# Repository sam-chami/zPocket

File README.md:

# zPocket
> WIP

The zPocket is a modular, handheld portable Linux device with a square touchscreen as well as keyboard for input. The modularity allows you to use it as a Cyberdeck, Phone, or even satellite communicator.

## Significant features:
- Touchscreen 720x720 panel
- Blackberry Q10 Keyboard
- Raspberry Pi Compute Module 5
- Mini PCIe connector
- USB-C Dual-role Port and mini HDMI
- Magnetometer (Compass)
- Battery Charging and Gauge

## Assembly Render
Front                                                   |  Back
:------------------------------------------------------:|:--------------------------------------:
  |  

## PCB

## Documentation
The documentation is available in [this repository's wiki page](https://github.com/sam-chami/zPocket/wiki)

## License
The zPocket hardware has a "CERN Open Hardware Licence Version 2 - Strongly Reciprocal".

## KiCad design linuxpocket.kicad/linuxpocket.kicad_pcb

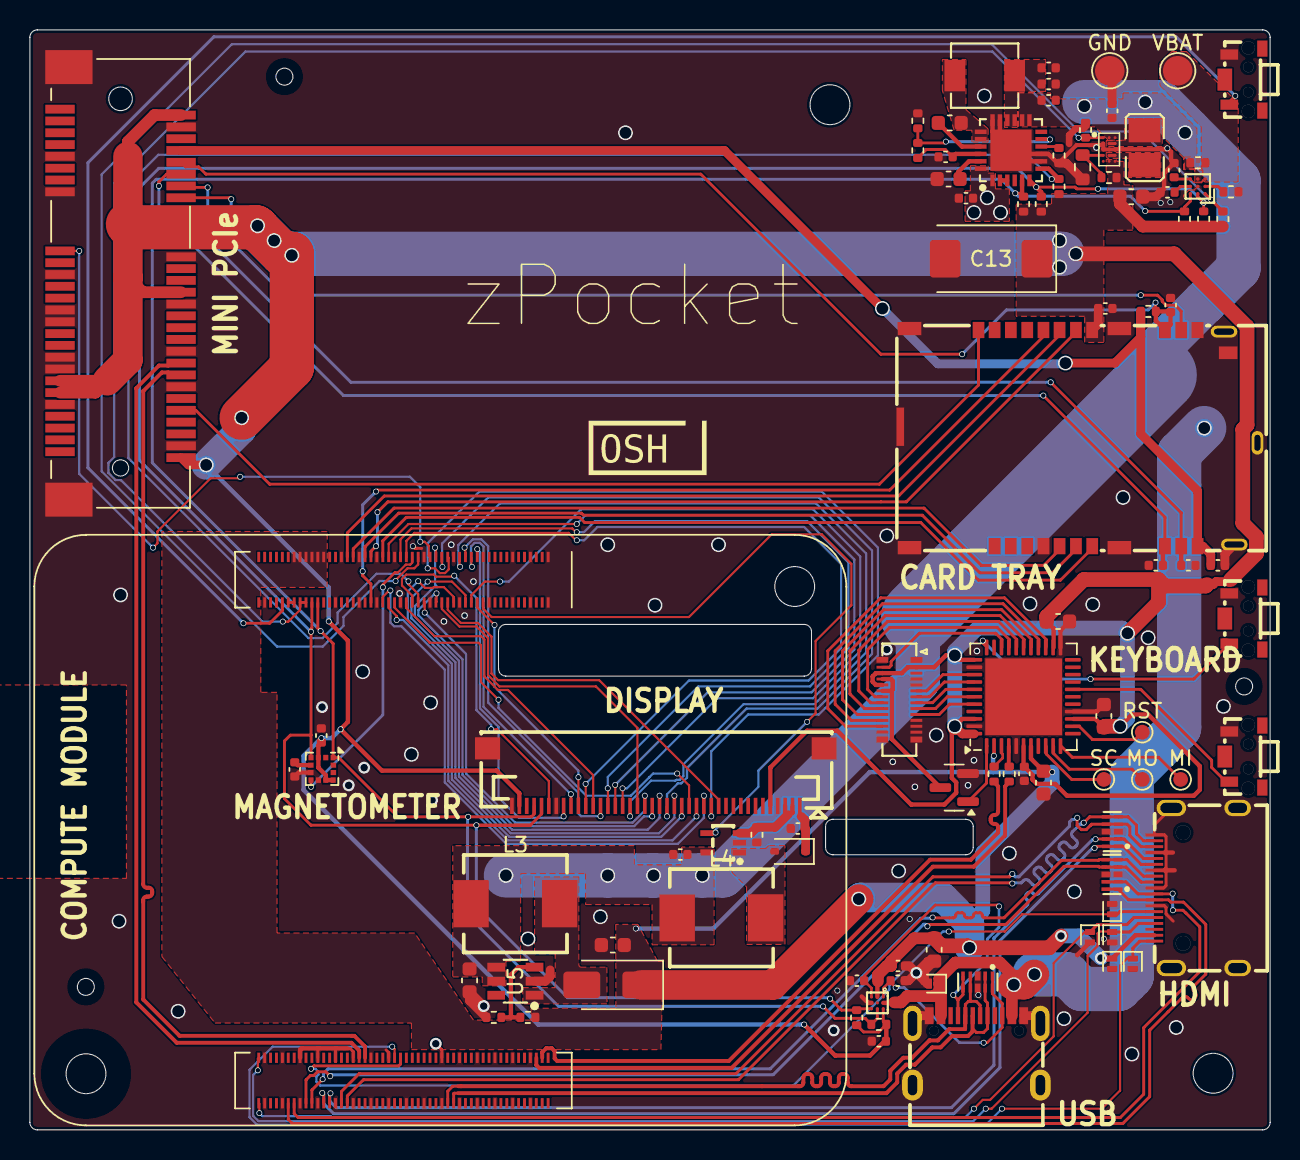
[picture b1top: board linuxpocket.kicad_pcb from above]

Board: 4 copper layers, 84.0 x 74.5 mm, 94 parts (0 on the bottom side), 112 nets.

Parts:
C1, C4, C6, C7, C11, C32: 10uF; C_0402_1005Metric
C2, C10, C17, C18, C19, C22, C27, C28: 1uF; C_0402_1005Metric
C3, C23, C24, C25: 47nF; C_0603_1608Metric
C5, C9: 4.7uF; C_0402_1005Metric
C8, C12, C20, C21, C26: 22uF; C_0603_1608Metric
C13: 470uF; CP_EIA-7343-31_Kemet-D
C14, C15, C16: 33pF; C_0402_1005Metric
C29, C30: 220pF; C_0402_1005Metric
C31: 220nF; C_0402_1005Metric
D2: D_Schottky; D_SOD-323
D3: D_Schottky; D_SMA
D4, D5, D11: TPD4E02B04DQAR; USON-10_L2.5-W1.0-P0.50-BL
D6, D7, D8, D9, D10, D12: H5VL10B; D_SOD-882
FPC1: XF2M-4015-1A_C225713; FPC-SMD_40P-P0.50_L4.9-W23.5
GND: TestPoint_Pad_D2.0mm
J1: XDSM-1035-08-KT; SIM-SMD_XDSM-1035-08_1
J2: Bus_PCI_Express_Mini; BUS_PCI_Express_Mini_Full
J3: HDMI_C_1.4; HDMI-SMD_A71-05H4-111N1
J4: USB_C_Receptacle_USB2.0_14P; USB-SMD_TYPE-C16PIN-1
L1: 2.2uH; IND-SMD_L4.4-W4.2
L2: 0.47uH; L1008
L3, L4: 4.7uH; IND-SMD_L7.0-W6.6
MI: TestPoint; TestPoint_Pad_D1.0mm
MO: TestPoint; TestPoint_Pad_D1.0mm
Module1: ComputeModule4-CM4; Raspberry-Pi-4-Compute-Module
Q1: MMBT3904; SOT-23
R1, R2, R3, R8, R9, R10, R11, R15, R16, R21: 10k; R_0402_1005Metric
R4, R22: 22; R_0402_1005Metric
R6: 120; R_0402_1005Metric
R7, R20: 15k; R_0402_1005Metric
R12: 10mΩ; R_0402_1005Metric
R13: 510k; R_0402_1005Metric
R14: 91k; R_0603_1608Metric
R18: 4.7; R_0402_1005Metric
R19: 100k; R_0402_1005Metric
R26, R27: 4.7k; R_0402_1005Metric
RST: TestPoint; TestPoint_Pad_D1.0mm
SC: TestPoint; TestPoint_Pad_D1.0mm
SW1, SW2, SW3: PUSH; SW-SMD_GT-TC020B-H035-L05
U1: BQ24295RGER; VQFN-24_L4.0-W4.0-P0.50-TL-EP2.8
U2: BQ27426YZFR; DSBGA-9_L1.5-W1.5-R3-C3-P0.50-BL
U3: TPS63805YFFR; DSBGA-15_L2.3-W1.3-R5-C3-P0.40-TL
U4: TPS61169DCKR; SC-70-5_L2.1-W1.3-P0.65-LS2.1-BR
U5: MT3608L; SOT-23-6_L2.9-W1.6-P0.95-LS2.8-BL_3
U6: FUSB302BUCX; WLCSP-9_L1.3-W1.2-R3-C3-P0.40-TL
U7: BBQ10KBD; BM14B(0.8)-24DS-0.4V(53)
U8: ATmega32U4-M; QFN-44-1EP_7x7mm_P0.5mm_EP5.2x5.2mm
U9: LIS2MDL; LGA-12_2x2mm_P0.5mm
VBAT: TestPoint_Pad_D2.0mm

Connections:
+1V8: Module1.88 (+1.8v_(Output)), Module1.90 (+1.8v_(Output))
+3V3: C1.2, C12.1, C13.1, C22.1, C23.1, C24.1, C27.2, C32.2, FPC1.5, FPC1.39, J1.16 (VDD), J2.2 (+3V3AUX), J2.24 (+3V3AUX), J2.39 (+3V3AUX), J2.41 (+3V3AUX), J2.52 (+3V3AUX), R1.1, R2.1, R3.1, R9.1, R10.1, R11.1, R13.1, R26.1, R27.1, U3.E2 (VOUT), U3.E3 (VOUT), U6.A3 (VDD), U7.2 (MIC_VDD), U7.24 (LEDA_3_4), U7.26 (LEDA_1_2), U8.6 (UCAP), U8.14 (VCC), U8.24 (AVCC), U8.34 (VCC), U8.42 (AREF), U8.44 (AVCC), U9.3 (~CS), U9.9 (Vdd), U9.10 (Vdd_IO)
+5V: C21.1, C25.1, C26.1, C28.2, D3.1 (K), D10.1 (A1), J3.18 (+5V), Module1.77 (+5v_(Input)), Module1.79 (+5v_(Input)), Module1.81 (+5v_(Input)), Module1.83 (+5v_(Input)), Module1.85 (+5v_(Input)), Module1.87 (+5v_(Input)), R19.1, U6.B1 (VCONN), U8.2 (UVCC), U8.7 (VBUS)
/Battery and Power/3V3 EN: Module1.78 (GPIO_VREF(1.8v/3.3v_Input)), Module1.84 (+3.3v_(Output)), Module1.86 (+3.3v_(Output)), R21.1, U3.A1 (EN)
/Battery and Power/BACKLIGHT: Module1.24 (GPIO26), U4.4 (CTRL)
/Battery and Power/CHARGE_INT: Module1.46 (GPIO22), R3.2, U1.7 (INT)
/Battery and Power/CHARGE_NTC: R7.1, R8.2, U1.11 (TS)
/Battery and Power/GAUGE_GPOUT: Module1.45 (GPIO24), R9.2, U2.A1 (GPOUT)
/Battery and Power/LEDA: C19.2, D2.1 (K), FPC1.1
/Battery and Power/LEDK: FPC1.2, FPC1.3, R18.1, U4.3 (FB)
/Battery and Power/REGN: C5.1, R8.1, U1.22 (REGN)
/Battery and Power/SYS: C6.1, C7.1, L1.1, U1.15 (SYS), U1.16 (SYS)
/Battery and Power/VBATT: C10.2, R12.1, U2.C1 (SRP), U2.C3 (BAT), VBAT.1
/Battery and Power/VBUS: C2.1, D12.1 (A1), J4.A4 (VBUS), J4.B9 (VBUS), U1.1 (VBUS), U1.24 (VBUS), U6.A2 (VBUS)
/Battery and Power/VBload: C4.1, C11.1, C18.2, C20.1, L3.1, L4.1, R12.2, U1.13 (BAT), U1.14 (BAT), U2.C2 (SRN), U3.A2 (VIN), U3.A3 (VIN), U4.5 (VIN), U5.4 (EN), U5.5 (VIN)
/Battery and Power/VDD: C9.1, U2.B3 (VDD)
/GPIO/DE: FPC1.13, Module1.35 (ID_SC)
/GPIO/DPI_D0: FPC1.16, Module1.54 (GPIO4)
/GPIO/DPI_D1: FPC1.17, Module1.34 (GPIO5)
/GPIO/DPI_D2: FPC1.18, Module1.30 (GPIO6)
/GPIO/DPI_D3: FPC1.19, Module1.37 (GPIO7)
/GPIO/DPI_D4: FPC1.20, Module1.39 (GPIO8)
/GPIO/DPI_D5: FPC1.21, Module1.40 (GPIO9)
/GPIO/DPI_D6: FPC1.22, Module1.44 (GPIO10)
/GPIO/DPI_D7: FPC1.23, Module1.38 (GPIO11)
/GPIO/DPI_D8: FPC1.24, Module1.31 (GPIO12)
/GPIO/DPI_D9: FPC1.25, Module1.28 (GPIO13)
/GPIO/DPI_D10: FPC1.26, Module1.55 (GPIO14)
/GPIO/DPI_D11: FPC1.27, Module1.51 (GPIO15)
/GPIO/DPI_D12: FPC1.28, Module1.29 (GPIO16)
/GPIO/DPI_D13: FPC1.29, Module1.50 (GPIO17)
/GPIO/DPI_D14: FPC1.30, Module1.49 (GPIO18)
/GPIO/DPI_D15: FPC1.31, Module1.26 (GPIO19)
/GPIO/DPI_D16: FPC1.32, Module1.27 (GPIO20)
/GPIO/DPI_D17: FPC1.33, Module1.25 (GPIO21)
/GPIO/LCD_HSYNC: FPC1.15, Module1.56 (GPIO3)
/GPIO/LCD_VSYNC: FPC1.14, Module1.58 (GPIO2)
/GPIO/MAG_INT: Module1.47 (GPIO23), U9.7 (DRDY)
/GPIO/PCLK: FPC1.12, Module1.36 (ID_SD)
/GPIO/PWR_BUT: Module1.92 (RUN_PG), SW1.1
/GPIO/RI: J2.17 (UIM_C8), Module1.41 (GPIO25)
/GPIO/SD_CLK: J1.17 (CLK), Module1.57 (SD_CLK)
/GPIO/SD_CMD: J1.15 (CMD), Module1.62 (SD_CMD)
/GPIO/SD_DAT0: J1.19 (DAT0), Module1.63 (SD_DAT0)
/GPIO/SD_DAT1: J1.20 (DAT1), Module1.67 (SD_DAT1)
/GPIO/SD_DAT2: J1.13 (DAT2), Module1.69 (SD_DAT2)
/GPIO/SD_DAT3: J1.14 (CD/DAT3), Module1.61 (SD_DAT3)
/GPIO/SIM_CLK: C14.1, J1.3 (SIM1_CLK), J2.12 (UIM_CLK)
/GPIO/SIM_IO: C15.1, J1.6 (SIM1_I/O), J2.10 (UIM_DATA), R15.2
/GPIO/SIM_RST: C16.1, J1.2 (SIM1_RST), J2.14 (~UIM_RESET)
/GPIO/SIM_VCC: C17.1, J1.1 (SIM1_VCC), J2.8 (UIM_PWR), R15.1
/GPIO/SIM_VPP: J1.5 (SIM1_VPP), J2.16 (UIM_VPP)
/GPIO/TP_INT: FPC1.35, Module1.48 (GPIO27)
/GPIO/TRAY_SW: J1.21 (SW), J2.44 (~LED_WLAN)
/GPIO/VOL_DOWN: SW3.1, U8.18 (PD0)
/GPIO/VOL_UP: SW2.1, U8.33 (~HWB/PE2)
/High Speed/HDMI_CEC: D6.1 (A1), J3.14 (CEC), Module1.151 (HDMI0_CEC)
/High Speed/HDMI_CLK+: D5.2 (IO2), D5.9 (NC), J3.11 (CK+), Module1.188 (HDMI0_CLK_P)
/High Speed/HDMI_CLK-: D5.1 (IO1), D5.10 (NC), J3.12 (CK-), Module1.190 (HDMI0_CLK_N)
/High Speed/HDMI_HP: D9.1 (A1), J3.19 (HPD/HEAC-), Module1.153 (HDMI0_HOTPLUG)
/High Speed/HDMI_SCL: D7.1 (A1), J3.15 (SCL), Module1.200 (HDMI0_SCL)
/High Speed/HDMI_SDA: D8.1 (A1), J3.16 (SDA), Module1.199 (HDMI0_SDA)
/High Speed/HDMI_TX0+: D5.5 (IO4), D5.6 (NC), J3.8 (D0+), Module1.182 (HDMI0_TX0_P)
/High Speed/HDMI_TX0-: D5.4 (IO3), D5.7 (NC), J3.9 (D0-), Module1.184 (HDMI0_TX0_N)
/High Speed/HDMI_TX1+: D4.2 (IO2), D4.9 (NC), J3.5 (D1+), Module1.176 (HDMI0_TX1_P)
/High Speed/HDMI_TX1-: D4.1 (IO1), D4.10 (NC), J3.6 (D1-), Module1.178 (HDMI0_TX1_N)
/High Speed/HDMI_TX2+: D4.5 (IO4), D4.6 (NC), J3.2 (D2+), Module1.170 (HDMI0_TX2_P)
/High Speed/HDMI_TX2-: D4.4 (IO3), D4.7 (NC), J3.3 (D2-), Module1.172 (HDMI0_TX2_N)
/High Speed/USB2-D_N: Module1.103 (USB2_N), R4.2
/High Speed/USB2-D_P: Module1.105 (USB2_P), R22.1
/High Speed/USB3-0-D_N: D11.4 (IO3), D11.7 (NC), J4.A7 (D-), J4.B7 (D-), Module1.136 (CAM0_D1_P)
/High Speed/USB3-0-D_P: D11.2 (IO2), D11.9 (NC), J4.A6 (D+), J4.B6 (D+), Module1.134 (CAM0_D1_N)
/High Speed/USB3-1-D_N: J2.36 (USB_D-), Module1.165 (DSI0_D1_P)
/High Speed/USB3-1-D_P: J2.38 (USB_D+), Module1.163 (DSI0_D1_N)
/Keyboard/MISO: MI.1, U8.11 (PB3)
/Keyboard/MOSI: MO.1, U8.10 (PB2)
/Keyboard/RESET: RST.1, U8.13 (~RESET)
/Keyboard/SCK: SC.1, U8.9 (PB1)
/SCL: FPC1.37, Module1.80 (SCL0), R1.2, R11.2, R27.2, U1.5 (SCL), U2.A3 (SCL), U6.B3 (SCL), U9.1 (SCL/SPC)
/SDA: FPC1.36, Module1.82 (SDA0), R2.2, R10.2, R26.2, U1.6 (SDA), U2.A2 (SDA), U6.C3 (SDA), U9.4 (SDA/SDI/SDO)
/hs_io/CC1: C29.1, D11.5 (IO4), D11.6 (NC), J4.A5 (CC1), U6.C1 (CC1)
/hs_io/CC2: C30.1, D11.1 (IO1), D11.10 (NC), J4.B5 (CC2), U6.A1 (CC2)
GND: C1.1, C2.2, C4.2, C5.2, C6.2, C7.2, C8.1, C9.2, C10.1, C11.2, C12.2, C13.2, C14.2, C15.2, C16.2, C17.2, C18.1, C19.1, C20.2, C21.2, C22.2, C23.2, C24.2, C25.2, C26.2, C27.1, C28.1, C29.2, C30.2, C31.2, C32.1, D4.3 (GND), D4.8 (GND), D5.3 (GND), D5.8 (GND), D6.2 (A2), D7.2 (A2), D8.2 (A2), D9.2 (A2), D10.2 (A2), D11.3 (GND), D11.8 (GND), D12.2 (A2), FPC1.0, FPC1.4, FPC1.34, FPC1.40, GND.1, J1.4 (SIM1_GND), J1.18 (VSS), J1.22 (GND), J1.23 (GND), J1.24 (GND), J1.25 (GND), J1.26 (GND), J1.27 (GND), J1.28 (GND), J1.29 (GND), J1.30 (GND), J2.4 (GND), J2.9 (GND), J2.15 (GND), J2.18 (GND), J2.21 (GND), J2.26 (GND), J2.27 (GND), J2.29 (GND), J2.34 (GND), J2.35 (GND), J2.37 (GND), J2.40 (GND), J2.43 (GND), J2.50 (GND), J2.MP, J3.1 (D2S), J3.4 (D1S), J3.7 (D0S), J3.10 (CKS), J3.13 (GND), J3.20, J3.21, J3.22, J3.23, J4.A1 (GND), J4.B1 (GND), J4.S1 (SHIELD), Module1.1 (GND), Module1.2 (GND), Module1.7 (GND), Module1.8 (GND), Module1.13 (GND), Module1.14 (GND), Module1.22 (GND), Module1.23 (GND), Module1.32 (GND), Module1.33 (GND), Module1.42 (GND), Module1.43 (GND), Module1.52 (GND), Module1.53 (GND), Module1.59 (GND), Module1.60 (GND), Module1.65 (GND), Module1.66 (GND), Module1.71 (GND), Module1.74 (GND), Module1.98 (GND), Module1.107 (GND), Module1.108 (GND), Module1.113 (GND), Module1.114 (GND), Module1.119 (GND), Module1.120 (GND), Module1.125 (GND), Module1.126 (GND), Module1.131 (GND), Module1.132 (GND), Module1.137 (GND), Module1.138 (GND), Module1.144 (GND), Module1.150 (GND), Module1.155 (GND), Module1.156 (GND), Module1.161 (GND), Module1.162 (GND), Module1.167 (GND), Module1.168 (GND), Module1.173 (GND), Module1.174 (GND), Module1.179 (GND), Module1.180 (GND), Module1.185 (GND), Module1.186 (GND), Module1.191 (GND), Module1.192 (GND), Module1.197 (GND), Module1.198 (GND), Q1.2 (E), R6.2, R7.2, R14.2, R16.2, R18.2, R20.2, R21.2, SW1.2, SW2.2, SW3.2, U1.8 (OTG), U1.9 (CE), U1.17 (PGND), U1.18 (PGND), U1.25 (EP), U2.B2 (VSS), U3.B1 (MODE), U3.C1 (AGND), U3.C2 (GND), U3.C3 (GND), U4.2 (GND), U5.2 (GND), U6.C2 (GND), U7.1 (GND), U7.4 (AGND), U7.5 (GND), U7.11 (GND), U7.12 (GND), U7.13 (GND), U7.14 (GND), U7.15 (GND), U7.16 (GND), U7.28 (GND), U8.5 (UGND), U8.15 (GND), U8.23 (GND), U8.35 (GND), U8.43 (GND), U8.45 (GND), U9.6 (GND), U9.8 (GND)
unnamed: C3.1, L1.2, U1.19 (SW), U1.20 (SW)
unnamed: D2.2 (A), L4.2, U4.1 (SW)
unnamed: D3.2 (A), L3.2, U5.1 (SW)
unnamed: L2.1, U3.B2 (L1), U3.B3 (L1)
unnamed: L2.2, U3.D2 (L2), U3.D3 (L2)
unnamed: Q1.1 (B), U8.1 (PE6)
unnamed: Q1.3 (C), U7.23 (LEDK_2_3), U7.25 (LEDK_1_4)
unnamed: C3.2, U1.21 (BTST)
unnamed: U1.2 (D+), U1.3 (D-)
unnamed: R6.1, U1.10 (ILIM)
unnamed: C8.2, U1.23 (PMID)
unnamed: R16.1, U2.B1 (BIN)
unnamed: R13.2, R14.1, U3.D1 (FB)
unnamed: R19.2, R20.1, U5.3 (FB)
unnamed: U7.7 (COL1), U8.37 (PF6)
unnamed: U7.9 (COL2), U8.39 (PF4)
unnamed: U7.10 (COL3), U8.40 (PF1)
unnamed: U7.17 (COL4), U8.25 (PD4)
unnamed: U7.19 (COL5), U8.27 (PD7)
unnamed: U7.6 (ROW1), U8.36 (PF7)
unnamed: U7.8 (ROW2), U8.38 (PF5)
unnamed: U7.18 (ROW3), U8.26 (PD6)
unnamed: U7.20 (ROW4), U8.28 (PB4)
unnamed: U7.21 (ROW5), U8.29 (PB5)
unnamed: U7.22 (ROW6), U8.30 (PB6)
unnamed: U7.27 (ROW7), U8.31 (PC6)
unnamed: R22.2, U8.4 (D+)
unnamed: R4.1, U8.3 (D-)
unnamed: C31.1, U9.5 (C1)

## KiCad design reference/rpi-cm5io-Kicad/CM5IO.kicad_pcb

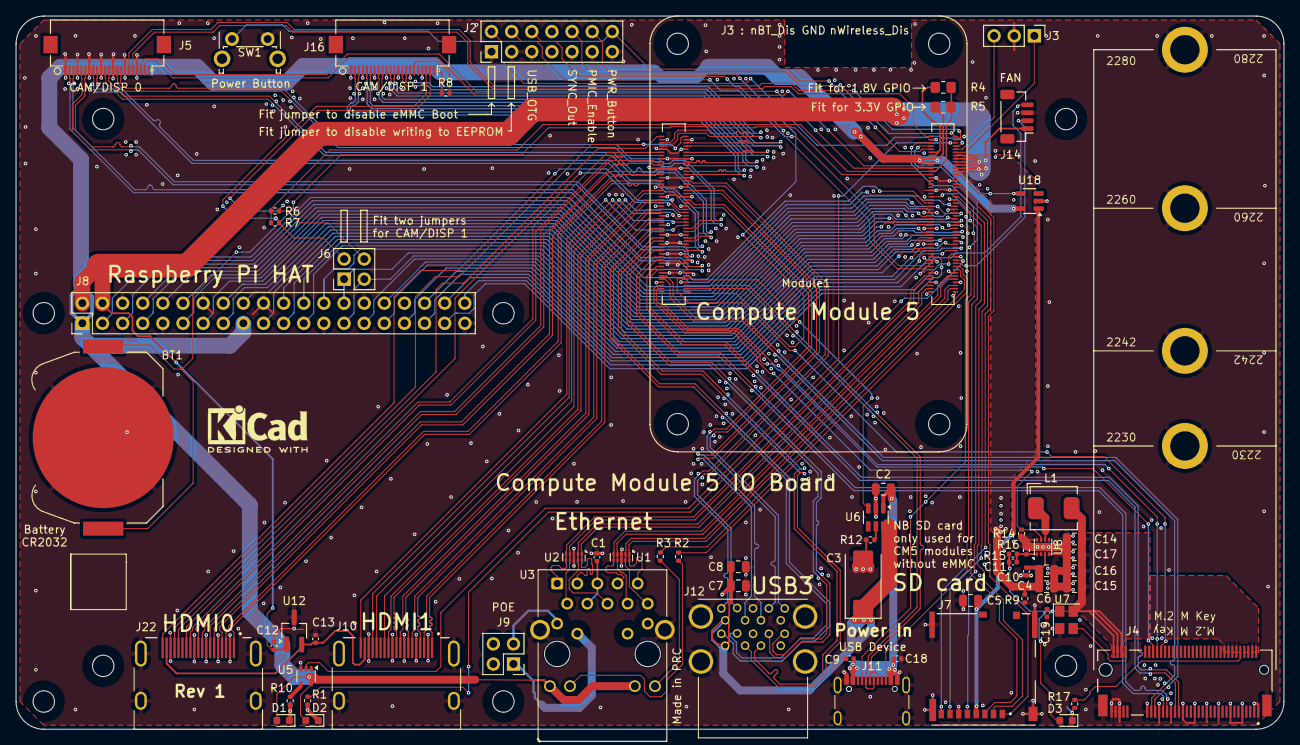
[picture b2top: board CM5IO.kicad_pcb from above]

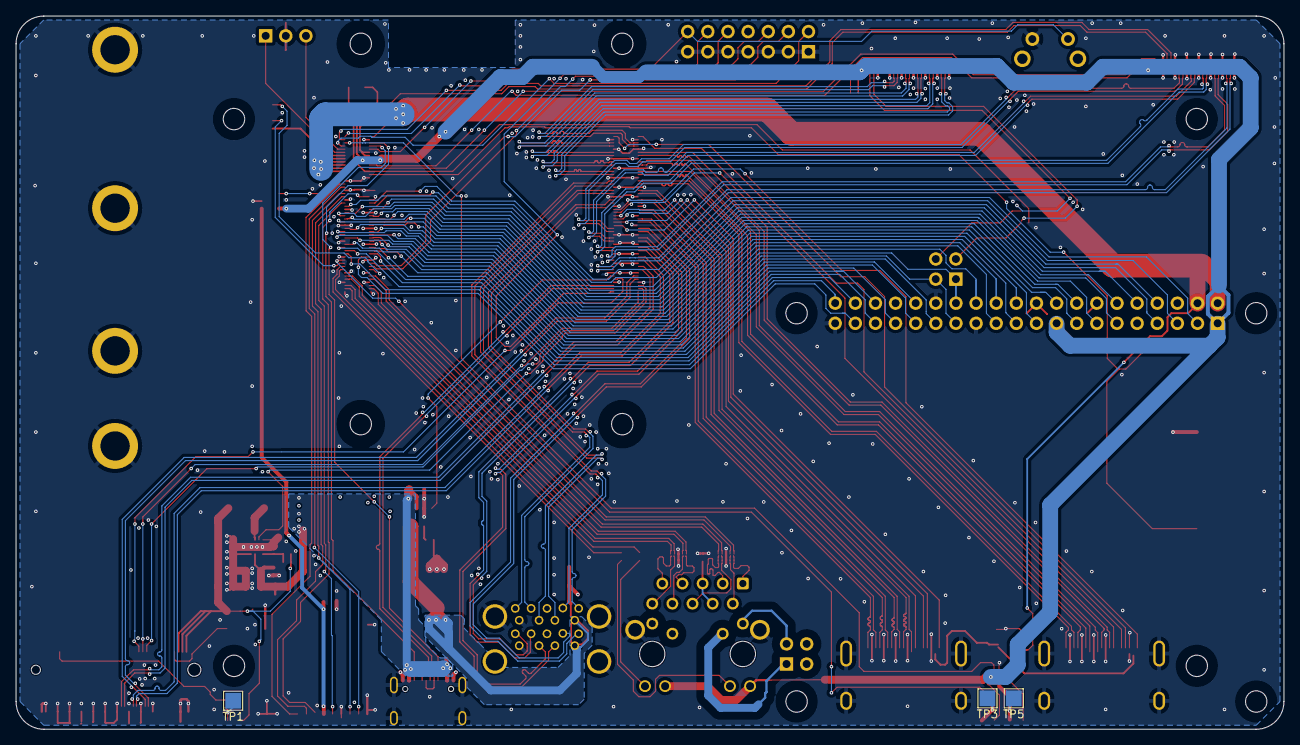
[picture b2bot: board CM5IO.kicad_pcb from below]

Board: 4 copper layers, 160.0 x 90.0 mm, 76 parts (3 on the bottom side), 161 nets.

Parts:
BT1: Battery_Cell; BatteryHolder_Keystone_3034_1x20mm
C1, C9, C10, C12, C13, C18, C19: 100n; C_0402_1005Metric
C2, C4, C5, C6, C7, C8, C14, C15, C16, C17: 10u; C_0805_2012Metric
C3: 100uF; CP_EIA-7343-31_Kemet-D
C11: 4.7nF; C_0402_1005Metric
D1: LED Red; LED_0603_1608Metric
D2, D3: LED Green; LED_0603_1608Metric
H1, H2, H3, H4, H5, H6, H7, H8: MountingHole; MountingHole_2.7mm_M2.5_DIN965
J2: Conn_02x07_Odd_Even; PinHeader_2x07_P2.54mm_Vertical
J3: Conn_01x03; PinHeader_1x03_P2.54mm_Vertical
J4: Bus_M.2_Socket_M; M.2 M Key socket
J5, J16: Conn_01x22_Female; Hirose_FH12-22S-0.5SH_1x22-1MP_P0.50mm_Horizontal
J6, J9: THD-02-R; PinHeader_2x02_P2.54mm_Vertical
J7: Micro_SD_Card_Det; SDCARD_MOLEX_503398-1892
J8: THD-20-R; PinHeader_2x20_P2.54mm_Vertical
J10, J22: 690-019-298-412; EDAC 690-019-298-412
J11: USB_C_Receptacle_USB2.0; USB_C_Receptacle_GCT_USB4105-xx-A_16P_TopMnt_Horizontal
J12: USB3_A; MTCONN_UBAF30-D2011
J14: JST_SHBM04B-SRSS-TB; JST_SH_BM04B-SRSS-TB_1x04-1MP_P1.00mm_Vertical
L1: 2.2uH; L_Bourns_SRP5030CC
Module1: ComputeModule5-CM5; Raspberry-Pi-5-Compute-Module
R1, R10, R17: 1k; R_0402_1005Metric
R2, R3: 470R; R_0402_1005Metric
R4: nf; R_0805_2012Metric_Pad1.20x1.40mm_HandSolder
R5: 0R; R_0805_2012Metric_Pad1.20x1.40mm_HandSolder
R6, R7, R8, R9, R16: 2.2K 1%; R_0402_1005Metric
R12: 15K 1%; R_0402_1005Metric
R14: 100K 1%; R_0402_1005Metric
R15: 10K 1%; R_0402_1005Metric
SW1: Right angle Tact button; SW_Tactile_SPST_Angled_PTS645Vx58-2LFS
TP1, TP3, TP5: TestPoint; TestPoint_Pad_2.0x2.0mm
U1, U2: TPD4EUSB30; USON-10_2.5x1.0mm_P0.5mm
U3: MagJack-A70-112-331N126; TRJG0926HENL
U5: 74LVC1G07SE-7; SOT-353_SC-70-5
U6: AP22653W6; SOT-23-6
U7: ASEK-32.768KHZ-L-R-T; Crystal_SMD_3225-4Pin_3.2x2.5mm
U8: AP3441SHE-7B; DFN-8-1EP_2x2mm_P0.5mm_EP1.05x1.75mm
U12: RT9742SNGV; TSOT-23_HandSoldering
U18: RT9742GGJ5; SOT-23-5
logo1: KiCad-Logo2_5mm_SilkScreen

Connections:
/+3.3v: D1.2 (A), D2.2 (A), J5.22, J8.1, J8.17, J16.22, Module1.84 (+3.3v_(Output)), Module1.86 (+3.3v_(Output)), R5.1, R8.1, U3.15 (LEDY_A), U3.17 (LEDG_A), U5.5 (VCC), U18.5 (IN)
/+5v: C2.1, C4.1, C6.1, C9.1, C10.1, C12.1, C18.1, J8.2, J8.4, J11.A4 (VBUS), J11.A9 (VBUS), J11.B4 (VBUS), J11.B9 (VBUS), J14.1, Module1.77 (+5v_(Input)), Module1.79 (+5v_(Input)), Module1.81 (+5v_(Input)), Module1.83 (+5v_(Input)), Module1.85 (+5v_(Input)), Module1.87 (+5v_(Input)), R9.1, U6.1 (IN), U8.3 (VIN), U12.1 (IN)
/CC1: J11.A5 (CC1), Module1.94 (CC1)
/CC2: J11.B5 (CC2), Module1.96 (CC2)
/CM5_GPIO ( Ethernet, GPIO, SDCARD)/+1.8v: Module1.88 (+1.8v_(Output)), Module1.90 (+1.8v_(Output)), R4.1
/CM5_GPIO ( Ethernet, GPIO, SDCARD)/BT_nDis: J3.3, Module1.91 (BT_nDisable)
/CM5_GPIO ( Ethernet, GPIO, SDCARD)/CAM_GPIO0: J5.17, Module1.97 (CAM_GPIO0)
/CM5_GPIO ( Ethernet, GPIO, SDCARD)/CAM_GPIO1: J5.18, Module1.100 (CAM_GPIO1)
/CM5_GPIO ( Ethernet, GPIO, SDCARD)/EEPROM_nWP: J2.4, Module1.20 (EEPROM_nWP)
/CM5_GPIO ( Ethernet, GPIO, SDCARD)/ETH_LEDG: Module1.17 (Ethernet_nLED2(3.3v)), R2.2
/CM5_GPIO ( Ethernet, GPIO, SDCARD)/ETH_LEDY: Module1.15 (Ethernet_nLED3(3.3v)), R3.2
/CM5_GPIO ( Ethernet, GPIO, SDCARD)/GPIO2: J8.3, Module1.58 (GPIO2)
/CM5_GPIO ( Ethernet, GPIO, SDCARD)/GPIO3: J8.5, Module1.56 (GPIO3)
/CM5_GPIO ( Ethernet, GPIO, SDCARD)/GPIO4: J8.7, Module1.54 (GPIO4)
/CM5_GPIO ( Ethernet, GPIO, SDCARD)/GPIO5: J8.29, Module1.34 (GPIO5)
/CM5_GPIO ( Ethernet, GPIO, SDCARD)/GPIO6: J8.31, Module1.30 (GPIO6)
/CM5_GPIO ( Ethernet, GPIO, SDCARD)/GPIO7: J8.26, Module1.37 (GPIO7)
/CM5_GPIO ( Ethernet, GPIO, SDCARD)/GPIO8: J8.24, Module1.39 (GPIO8)
/CM5_GPIO ( Ethernet, GPIO, SDCARD)/GPIO9: J8.21, Module1.40 (GPIO9)
/CM5_GPIO ( Ethernet, GPIO, SDCARD)/GPIO10: J8.19, Module1.44 (GPIO10)
/CM5_GPIO ( Ethernet, GPIO, SDCARD)/GPIO11: J8.23, Module1.38 (GPIO11)
/CM5_GPIO ( Ethernet, GPIO, SDCARD)/GPIO12: J8.32, Module1.31 (GPIO12)
/CM5_GPIO ( Ethernet, GPIO, SDCARD)/GPIO13: J8.33, Module1.28 (GPIO13)
/CM5_GPIO ( Ethernet, GPIO, SDCARD)/GPIO14: J8.8, Module1.55 (GPIO14)
/CM5_GPIO ( Ethernet, GPIO, SDCARD)/GPIO15: J8.10, Module1.51 (GPIO15)
/CM5_GPIO ( Ethernet, GPIO, SDCARD)/GPIO16: J8.36, Module1.29 (GPIO16)
/CM5_GPIO ( Ethernet, GPIO, SDCARD)/GPIO17: J8.11, Module1.50 (GPIO17)
/CM5_GPIO ( Ethernet, GPIO, SDCARD)/GPIO18: J8.12, Module1.49 (GPIO18)
/CM5_GPIO ( Ethernet, GPIO, SDCARD)/GPIO19: J8.35, Module1.26 (GPIO19)
/CM5_GPIO ( Ethernet, GPIO, SDCARD)/GPIO20: J8.38, Module1.27 (GPIO20)
/CM5_GPIO ( Ethernet, GPIO, SDCARD)/GPIO21: J8.40, Module1.25 (GPIO21)
/CM5_GPIO ( Ethernet, GPIO, SDCARD)/GPIO22: J8.15, Module1.46 (GPIO22)
/CM5_GPIO ( Ethernet, GPIO, SDCARD)/GPIO23: J8.16, Module1.47 (GPIO23)
/CM5_GPIO ( Ethernet, GPIO, SDCARD)/GPIO24: J8.18, Module1.45 (GPIO24)
/CM5_GPIO ( Ethernet, GPIO, SDCARD)/GPIO25: J8.22, Module1.41 (GPIO25)
/CM5_GPIO ( Ethernet, GPIO, SDCARD)/GPIO26: J8.37, Module1.24 (GPIO26)
/CM5_GPIO ( Ethernet, GPIO, SDCARD)/GPIO27: J8.13, Module1.48 (GPIO27)
/CM5_GPIO ( Ethernet, GPIO, SDCARD)/GPIO_VREF: Module1.78 (GPIO_VREF(1.8v/3.3v_Input)), R4.2, R5.2, R6.1, R7.1
/CM5_GPIO ( Ethernet, GPIO, SDCARD)/ID_SC: J6.1, J8.28, Module1.35 (ID_SC)
/CM5_GPIO ( Ethernet, GPIO, SDCARD)/ID_SD: J6.3, J8.27, Module1.36 (ID_SD)
/CM5_GPIO ( Ethernet, GPIO, SDCARD)/PMIC_ENABLE: J2.12, Module1.99 (PMIC_ENABLE)
/CM5_GPIO ( Ethernet, GPIO, SDCARD)/PWM: J14.2, Module1.19 (FAN_PWM)
/CM5_GPIO ( Ethernet, GPIO, SDCARD)/PWR_BUT: J2.14, Module1.92 (PWR_BUT), SW1.1
/CM5_GPIO ( Ethernet, GPIO, SDCARD)/SD_CLK: J7.5 (CLK), Module1.57 (SD_CLK)
/CM5_GPIO ( Ethernet, GPIO, SDCARD)/SD_CMD: J7.3 (CMD), Module1.62 (SD_CMD)
/CM5_GPIO ( Ethernet, GPIO, SDCARD)/SD_DAT0: J7.7 (DAT0), Module1.63 (SD_DAT0)
/CM5_GPIO ( Ethernet, GPIO, SDCARD)/SD_DAT1: J7.8 (DAT1), Module1.67 (SD_DAT1)
/CM5_GPIO ( Ethernet, GPIO, SDCARD)/SD_DAT2: J7.1 (DAT2), Module1.69 (SD_DAT2)
/CM5_GPIO ( Ethernet, GPIO, SDCARD)/SD_DAT3: J7.2 (DAT3/CD), Module1.61 (SD_DAT3)
/CM5_GPIO ( Ethernet, GPIO, SDCARD)/SD_PWR: C5.1, J7.4 (VDD), U18.1 (OUT)
/CM5_GPIO ( Ethernet, GPIO, SDCARD)/SD_PWR_ON: Module1.75 (SD_PWR_ON), U18.4 (EN)
/CM5_GPIO ( Ethernet, GPIO, SDCARD)/SYNC_OUT: J2.6, Module1.18 (Ethernet_SYNC_OUT(1.8v))
/CM5_GPIO ( Ethernet, GPIO, SDCARD)/TACHO: J14.4, Module1.16 (FAN_TACHO)
/CM5_GPIO ( Ethernet, GPIO, SDCARD)/TR0_TAP: J9.3, U3.11 (VC1)
/CM5_GPIO ( Ethernet, GPIO, SDCARD)/TR1_TAP: J9.1, U3.12 (VC2)
/CM5_GPIO ( Ethernet, GPIO, SDCARD)/TR2_TAP: J9.2, U3.13 (VC3)
/CM5_GPIO ( Ethernet, GPIO, SDCARD)/TR3_TAP: J9.4, U3.14 (VC4)
/CM5_GPIO ( Ethernet, GPIO, SDCARD)/TRD0_N: Module1.10 (Ethernet_Pair0_N), U2.4 (D2+), U2.7, U3.2 (TRD0-)
/CM5_GPIO ( Ethernet, GPIO, SDCARD)/TRD0_P: Module1.12 (Ethernet_Pair0_P), U2.5 (D2-), U2.6, U3.1 (TRD0+)
/CM5_GPIO ( Ethernet, GPIO, SDCARD)/TRD1_N: Module1.6 (Ethernet_Pair1_N), U2.2 (D1-), U2.9, U3.6 (TRD1-)
/CM5_GPIO ( Ethernet, GPIO, SDCARD)/TRD1_P: Module1.4 (Ethernet_Pair1_P), U2.1 (D1+), U2.10, U3.3 (TRD1+)
/CM5_GPIO ( Ethernet, GPIO, SDCARD)/TRD2_N: Module1.9 (Ethernet_Pair2_N), U1.4 (D2+), U1.7, U3.8 (TRD2-)
/CM5_GPIO ( Ethernet, GPIO, SDCARD)/TRD2_P: Module1.11 (Ethernet_Pair2_P), U1.5 (D2-), U1.6, U3.7 (TRD2+)
/CM5_GPIO ( Ethernet, GPIO, SDCARD)/TRD3_N: Module1.5 (Ethernet_Pair3_N), U1.2 (D1-), U1.9, U3.10 (TRD3-)
/CM5_GPIO ( Ethernet, GPIO, SDCARD)/TRD3_P: Module1.3 (Ethernet_Pair3_P), U1.1 (D1+), U1.10, U3.9 (TRD3+)
/CM5_GPIO ( Ethernet, GPIO, SDCARD)/USBOTG: J2.10, Module1.101 (USB_OTG_ID)
/CM5_GPIO ( Ethernet, GPIO, SDCARD)/VBAT: BT1.1 (+), Module1.76 (VBAT)
/CM5_GPIO ( Ethernet, GPIO, SDCARD)/WL_nDis: J3.1, Module1.89 (WiFi_nDisable)
/CM5_GPIO ( Ethernet, GPIO, SDCARD)/nPWR_LED: Module1.95 (LED_nPWR), U5.2
/CM5_GPIO ( Ethernet, GPIO, SDCARD)/nRPIBOOT: J2.2, Module1.93 (nRPIBOOT)
/CM5_HighSpeed/DPHY0_C_N: J5.8, Module1.127 (DPHY0_C_N)
/CM5_HighSpeed/DPHY0_C_P: J5.9, Module1.129 (DPHY0_C_P)
/CM5_HighSpeed/DPHY0_D0_N: J5.2, Module1.115 (DPHY0_D0_N)
/CM5_HighSpeed/DPHY0_D0_P: J5.3, Module1.117 (DPHY0_D0_P)
/CM5_HighSpeed/DPHY0_D1_N: J5.5, Module1.121 (DPHY0_D1_N)
/CM5_HighSpeed/DPHY0_D1_P: J5.6, Module1.123 (DPHY0_D1_P)
/CM5_HighSpeed/DPHY0_D2_N: J5.11, Module1.133 (DPHY0_D2_N)
/CM5_HighSpeed/DPHY0_D2_P: J5.12, Module1.135 (DPHY0_D2_P)
/CM5_HighSpeed/DPHY0_D3_N: J5.14, Module1.139 (DPHY0_D3_N)
/CM5_HighSpeed/DPHY0_D3_P: J5.15, Module1.141 (DPHY0_D3_P)
/CM5_HighSpeed/DPHY1_C_N: J16.8, Module1.187 (DPHY1_C_N)
/CM5_HighSpeed/DPHY1_C_P: J16.9, Module1.189 (DPHY1_C_P)
/CM5_HighSpeed/DPHY1_D0_N: J16.2, Module1.175 (DPHY1_D0_N)
/CM5_HighSpeed/DPHY1_D0_P: J16.3, Module1.177 (DPHY1_D0_P)
/CM5_HighSpeed/DPHY1_D1_N: J16.5, Module1.181 (DPHY1_D1_N)
/CM5_HighSpeed/DPHY1_D1_P: J16.6, Module1.183 (DPHY1_D1_P)
/CM5_HighSpeed/DPHY1_D2_N: J16.11, Module1.193 (DPHY1_D2_N)
/CM5_HighSpeed/DPHY1_D2_P: J16.12, Module1.195 (DPHY1_D2_P)
/CM5_HighSpeed/DPHY1_D3_N: J16.14, Module1.194 (DPHY1_D3_N)
/CM5_HighSpeed/DPHY1_D3_P: J16.15, Module1.196 (DPHY1_D3_P)
/CM5_HighSpeed/HDMI0_CEC: J22.13 (CEC), Module1.151 (HDMI0_CEC)
/CM5_HighSpeed/HDMI0_CK_N: J22.12 (CK-), Module1.190 (HDMI0_CLK_N)
/CM5_HighSpeed/HDMI0_CK_P: J22.10 (CK+), Module1.188 (HDMI0_CLK_P)
/CM5_HighSpeed/HDMI0_D0_N: J22.9 (D0-), Module1.184 (HDMI0_TX0_N)
/CM5_HighSpeed/HDMI0_D0_P: J22.7 (D0+), Module1.182 (HDMI0_TX0_P)
/CM5_HighSpeed/HDMI0_D1_N: J22.6 (D1-), Module1.178 (HDMI0_TX1_N)
/CM5_HighSpeed/HDMI0_D1_P: J22.4 (D1+), Module1.176 (HDMI0_TX1_P)
/CM5_HighSpeed/HDMI0_D2_N: J22.3 (D2-), Module1.172 (HDMI0_TX2_N)
/CM5_HighSpeed/HDMI0_D2_P: J22.1 (D2+), Module1.170 (HDMI0_TX2_P)
/CM5_HighSpeed/HDMI0_HOTPLUG: J22.19 (HPD/HEAC-), Module1.153 (HDMI0_HOTPLUG)
/CM5_HighSpeed/HDMI0_SCL: J22.15 (SCL), Module1.200 (HDMI0_SCL)
/CM5_HighSpeed/HDMI0_SDA: J22.16 (SDA), Module1.199 (HDMI0_SDA)
/CM5_HighSpeed/HDMI1_CEC: J10.13 (CEC), Module1.149 (HDMI1_CEC)
/CM5_HighSpeed/HDMI1_CK_N: J10.12 (CK-), Module1.166 (HDMI1_CLK_N)
/CM5_HighSpeed/HDMI1_CK_P: J10.10 (CK+), Module1.164 (HDMI1_CLK_P)
/CM5_HighSpeed/HDMI1_D0_N: J10.9 (D0-), Module1.160 (HDMI1_TX0_N)
/CM5_HighSpeed/HDMI1_D0_P: J10.7 (D0+), Module1.158 (HDMI1_TX0_P)
/CM5_HighSpeed/HDMI1_D1_N: J10.6 (D1-), Module1.154 (HDMI1_TX1_N)
/CM5_HighSpeed/HDMI1_D1_P: J10.4 (D1+), Module1.152 (HDMI1_TX1_P)
/CM5_HighSpeed/HDMI1_D2_N: J10.3 (D2-), Module1.148 (HDMI1_TX2_N)
/CM5_HighSpeed/HDMI1_D2_P: J10.1 (D2+), Module1.146 (HDMI1_TX2_P)
/CM5_HighSpeed/HDMI1_HOTPLUG: J10.19 (HPD/HEAC-), Module1.143 (HDMI1_HOTPLUG)
/CM5_HighSpeed/HDMI1_SCL: J10.15 (SCL), Module1.147 (HDMI1_SCL)
/CM5_HighSpeed/HDMI1_SDA: J10.16 (SDA), Module1.145 (HDMI1_SDA)
/CM5_HighSpeed/HDMI_5v: C13.1, J10.18 (+5V), J22.18 (+5V), U12.2 (OUT)
/CM5_HighSpeed/PCIE_CLK_N: J4.53 (REFCLKn), Module1.112 (PCIe_CLK_N)
/CM5_HighSpeed/PCIE_CLK_P: J4.55 (REFCLKp), Module1.110 (PCIe_CLK_P)
/CM5_HighSpeed/PCIE_PWR_EN: Module1.106 (PCIE_PWR_EN), R14.1, U8.7 (EN)
/CM5_HighSpeed/PCIE_RX_N: J4.43 (PETp0), Module1.118 (PCIe_RX_N)
/CM5_HighSpeed/PCIE_RX_P: J4.41 (PETn0), Module1.116 (PCIe_RX_P)
/CM5_HighSpeed/PCIE_TX_N: J4.49 (PERp0), Module1.124 (PCIe_TX_N)
/CM5_HighSpeed/PCIE_TX_P: J4.47 (PERn0), Module1.122 (PCIe_TX_P)
/CM5_HighSpeed/PCIE_nCLKREQ: J4.52 (~CLKREQ), Module1.102 (PCIe_nCLKREQ)
/CM5_HighSpeed/PCIE_nRST: J4.50 (~PERST), Module1.109 (PCIe_nRST)
/CM5_HighSpeed/PCIE_nWAKE: J4.54 (~PEWAKE), Module1.104 (PCIE_nWAKE)
/CM5_HighSpeed/SCL0: J5.20, Module1.80 (SCL0)
/CM5_HighSpeed/SCL1: J6.2, J16.20, R7.2
/CM5_HighSpeed/SDA0: J5.21, Module1.82 (SDA0)
/CM5_HighSpeed/SDA1: J6.4, J16.21, R6.2
/CM5_HighSpeed/USB3-0-D_N: J12.A2 (D-), Module1.136 (USB3-0-D_N)
/CM5_HighSpeed/USB3-0-D_P: J12.A3 (D+), Module1.134 (USB3-0-D_P)
/CM5_HighSpeed/USB3-0-RX_N: J12.A6 (SSRX+), Module1.128 (USB3-0-RX_N)
/CM5_HighSpeed/USB3-0-RX_P: J12.A5 (SSRX-), Module1.130 (USB3-0-RX_P)
/CM5_HighSpeed/USB3-0-TX_N: J12.A9 (SSTX+), Module1.140 (USB3-0-TX_N)
/CM5_HighSpeed/USB3-0-TX_P: J12.A8 (SSTX-), Module1.142 (USB3-0-TX_P)
/CM5_HighSpeed/USB3-1-D_N: J12.B2 (D-), Module1.165 (USB3-1-D_N)
/CM5_HighSpeed/USB3-1-D_P: J12.B3 (D+), Module1.163 (USB3-1-D_P)
/CM5_HighSpeed/USB3-1-RX_N: J12.B6 (SSRX+), Module1.157 (USB3-1-RX_N)
/CM5_HighSpeed/USB3-1-RX_P: J12.B5 (SSRX-), Module1.159 (USB3-1-RX_P)
/CM5_HighSpeed/USB3-1-TX_N: J12.B9 (SSTX+), Module1.169 (USB3-1-TX_N)
/CM5_HighSpeed/USB3-1-TX_P: J12.B8 (SSTX-), Module1.171 (USB3-1-TX_P)
/CM5_HighSpeed/VBUS: C3.1, C7.1, C8.1, J12.A1 (VBUS), J12.B1 (VBUS), U6.6 (OUT)
/CM5_HighSpeed/VBUS_EN: Module1.111 (VBUS_EN), U6.3 (EN)
/PCIe-M2/FB: C11.2, R15.2, R16.1, U8.1 (FB)
/PCIe-M2/M2_3v3: C11.1, C14.1, C15.1, C16.1, C17.1, C19.1, D3.2 (A), J4.2 (3.3V), J4.4 (3.3V), J4.12 (3.3V), J4.14 (3.3V), J4.16 (3.3V), J4.18 (3.3V), J4.70 (3.3V), J4.72 (3.3V), J4.74 (3.3V), L1.2, R15.1, U7.1 (EN), U7.4 (VDD)
/USB2_N: J11.A7 (D-), J11.B7 (D-), Module1.103 (USB2_N)
/USB2_P: J11.A6 (D+), J11.B6 (D+), Module1.105 (USB2_P)
GND: BT1.2 (-), C1.2, C2.2, C3.2, C4.2, C5.2, C6.2, C7.2, C8.2, C9.2, C10.2, C12.2, C13.2, C14.2, C15.2, C16.2, C17.2, C18.2, C19.2, J2.1, J2.3, J2.5, J2.7, J2.9, J2.11, J2.13, J3.2, J4.1 (GND), J4.3 (GND), J4.9 (GND), J4.15 (GND), J4.21 (GND), J4.27 (GND), J4.33 (GND), J4.39 (GND), J4.45 (GND), J4.51 (GND), J4.57 (GND), J4.71 (GND), J4.73 (GND), J4.75 (GND), J4.M1 (GND2230), J4.M2 (GND2242), J4.M3 (GND2260), J4.M4 (GND2280), J4.S1, J4.S2, J5.1, J5.4, J5.7, J5.10, J5.13, J5.16, J5.19, J7.6 (VSS), J7.11 (SHIELD), J8.6, J8.9, J8.14, J8.20, J8.25, J8.30, J8.34, J8.39, J10.2 (D2S), J10.5 (D1S), J10.8 (D0S), J10.11 (CKS), J10.17 (GND), J10.SH1 (SH), J10.SH2 (SH), J10.SH3 (SH), J10.SH4 (SH), J11.A1 (GND), J11.A12 (GND), J11.B1 (GND), J11.B12 (GND), J11.S1 (SHIELD), J12.10 (SHIELD), J12.A4 (GND), J12.A7 (DRAIN), J12.B4 (GND), J12.B7 (DRAIN), J14.3, J16.1, J16.4, J16.7, J16.10, J16.13, J16.16, J16.19, J22.2 (D2S), J22.5 (D1S), J22.8 (D0S), J22.11 (CKS), J22.17 (GND), J22.SH1 (SH), J22.SH2 (SH), J22.SH3 (SH), J22.SH4 (SH), Module1.1 (GND), Module1.2 (GND), Module1.7 (GND), Module1.8 (GND), Module1.13 (GND), Module1.14 (GND), Module1.22 (GND), Module1.23 (GND), Module1.32 (GND), Module1.33 (GND), Module1.42 (GND), Module1.43 (GND), Module1.52 (GND), Module1.53 (GND), Module1.59 (GND), Module1.60 (GND), Module1.65 (GND), Module1.66 (GND), Module1.71 (GND), Module1.74 (GND), Module1.98 (GND), Module1.107 (GND), Module1.108 (GND), Module1.113 (GND), Module1.114 (GND), Module1.119 (GND), Module1.120 (GND), Module1.125 (GND), Module1.126 (GND), Module1.131 (GND), Module1.132 (GND), Module1.137 (GND), Module1.138 (GND), Module1.144 (GND), Module1.150 (GND), Module1.155 (GND), Module1.156 (GND), Module1.161 (GND), Module1.162 (GND), Module1.167 (GND), Module1.168 (GND), Module1.173 (GND), Module1.174 (GND), Module1.179 (GND), Module1.180 (GND), Module1.185 (GND), Module1.186 (GND), Module1.191 (GND), Module1.192 (GND), Module1.197 (GND), Module1.198 (GND), R9.2, R12.2, R14.2, R16.2, SW1.2, U1.3 (GND), U1.8 (GND), U2.3 (GND), U2.8 (GND), U3.19 (SHIELD), U3.20 (SHIELD), U5.3 (GND), U6.2 (GND), U7.2 (GND), U8.4 (PGND), U8.8 (SGND), U8.9 (PAD), U12.3 (GND), U18.2 (GND)
unnamed: C1.1, U3.4 (CT), U3.5 (CT)
unnamed: D1.1 (K), R10.1, TP5.1
unnamed: D2.1 (K), R1.1, TP3.1
unnamed: D3.1 (K), R17.1, TP1.1
unnamed: J4.10 (DAS/~DSS/~LED1), R17.2
unnamed: J4.68 (SUSCLK), U7.3 (Out)
unnamed: J16.17, R8.2
unnamed: Module1.21 (LED_nACT), R1.2
unnamed: R10.2, U5.4
unnamed: R3.1, U3.18 (LEDG_K)
unnamed: R2.1, U3.16 (LEDY_K)
unnamed: R12.1, U6.5 (ILIM)
unnamed: L1.1, U8.6 (LX)

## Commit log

2024-11-27 Initial.
2025-01-26 Add keyboard, improve many things etc.
2025-01-26 Keyboard done. (Except mic) #2
2025-01-28 Start with HDMI connector.
2025-01-29 Finish HDMI
2025-02-01 Finish USB-C. #1
2025-02-02 Add magnetometer #5. Add footprints to some symbols.
2025-02-02 Start placing components in PCB.
2025-02-25 PCB almost done and schematic finished.
2025-03-04 PCB basically finished.
2025-03-04 Add LICENSE
2025-03-04 Write README.md
2025-03-05 Move Images
2025-03-05 Start case design.
2025-03-06 Add display Technical Drawing.
2025-03-07 Progressing with case design.
2025-03-08 Improving Case design
2025-03-09 PCB fabrication info.
2025-03-14 Add certification to README.md
2025-03-14 PCB ordered, updated images

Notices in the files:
linuxpocket.kicad/linuxpocket.kicad_pcb:
Licensed under
CERN-OHL-S-2
